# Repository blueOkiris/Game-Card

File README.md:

# Game Card

## Description

A business card sized portable game console utilizing buttons, multiple games, and an i2c display

[YouTube Video](https://www.youtube.com/watch?v=qE-Pg2zxOUw)

## Improving the Design (HELP!)

Right now I'm trying to redesign a new version where I can source all the electronics from manufacturers for a few reasons including:
 * Putting them up for sale
 * Decreasing cost
 * Simplifying build time

I've got everything redesigned and sourced except for the display. These little OLEDs are available everywhere except distributers it seems, and while they're like \$1-3 usually, I can't find sourcable ones for PCBs under \$10.

When the rest of the electronics costs \$4 total, it seems insane for it to be almost $15 to make.

If you can find a source I can use to build this, PLEASE let me know!

## Game List

Currently there are three games developed for the Game Card:

- Ping (1 and 2 player pong clone)
- Snek (Snake clone)
- In Progress: Tiny RPG (a very small RPG)

## More Links
 - [Info on Design](/docs/DESIGN.md)
 - [Info on Programming Cartridges](/docs/PROGRAMMING.md)
 - [Hackaday Project Page](https://hackaday.io/project/178686-game-card)

NOTE: If you're looking for the PCB designs and parts for the cartridges and cards, they're on the hackaday page

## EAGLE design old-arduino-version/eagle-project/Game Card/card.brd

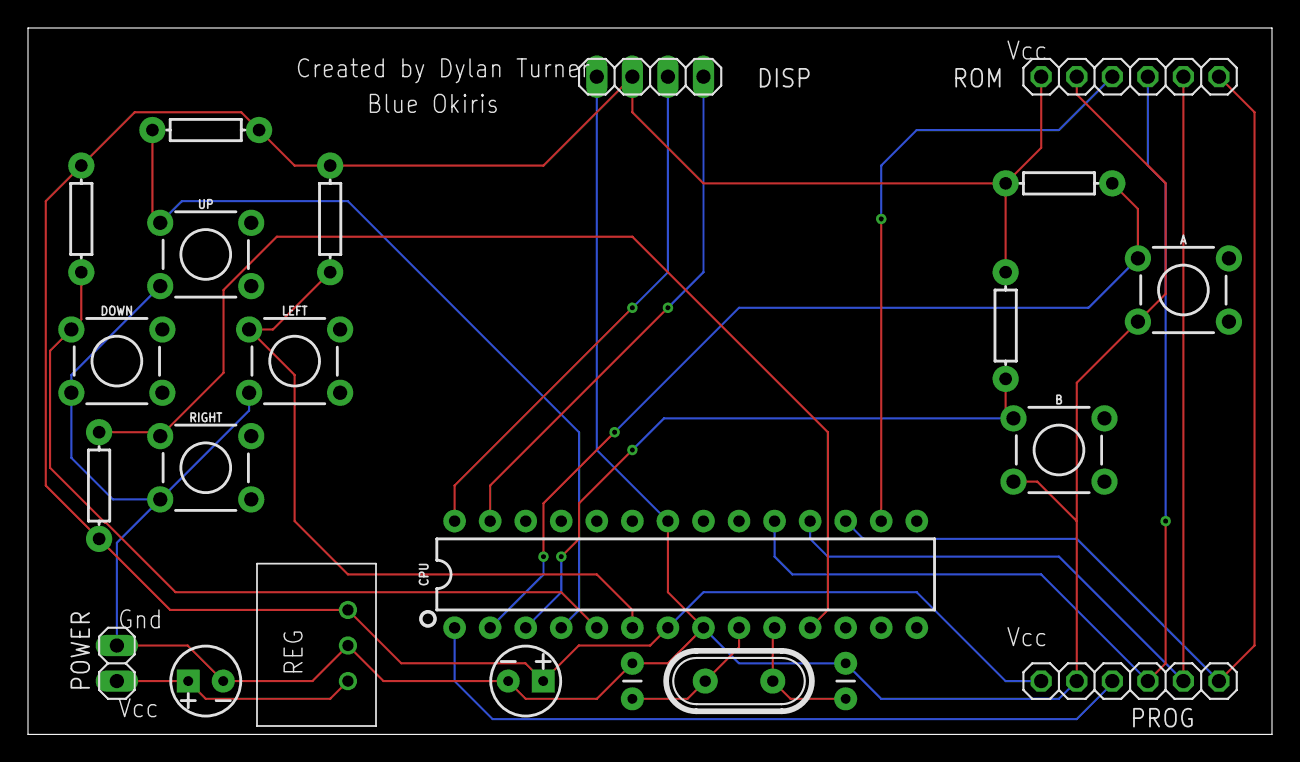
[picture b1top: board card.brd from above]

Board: 2 copper layers, 88.9 x 50.5 mm, 23 parts (0 on the bottom side), 18 nets.

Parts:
A: MOMENTARY-SWITCH-SPST-PTH-6.0MM; TACTILE_SWITCH_PTH_6.0MM
B: MOMENTARY-SWITCH-SPST-PTH-6.0MM; TACTILE_SWITCH_PTH_6.0MM
C1, C2: 10uF; CPOL-RADIAL-2.5MM-5MM
C3, C4: 22pF; CAP-PTH-2.54
CPU: 328P; DIP28
DISP: 1X04
DOWN: MOMENTARY-SWITCH-SPST-PTH-6.0MM; TACTILE_SWITCH_PTH_6.0MM
LEFT: MOMENTARY-SWITCH-SPST-PTH-6.0MM; TACTILE_SWITCH_PTH_6.0MM
POWER: 1X02
PROG: 1X06
R1, R2, R3, R4, R5, R6: 1k; AXIAL-0.3
REG: R-78E5.0-1.0; DC-DC_CONVERTER_78XX
RIGHT: MOMENTARY-SWITCH-SPST-PTH-6.0MM; TACTILE_SWITCH_PTH_6.0MM
ROM: 1X06
UP: MOMENTARY-SWITCH-SPST-PTH-6.0MM; TACTILE_SWITCH_PTH_6.0MM
X1: CRYSTALS-NOGND-HC49; HC49

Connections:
GND: A.3, B.3, C1.2, C2.2, C3.2, C4.2, CPU.8, CPU.22, DISP.1, DOWN.3, LEFT.3, POWER.1, PROG.2, REG.GND, RIGHT.3, ROM.2, UP.3
unnamed: CPU.17, PROG.6, ROM.6
unnamed: CPU.18, PROG.5, ROM.5
unnamed: CPU.19, PROG.4, ROM.4
unnamed: CPU.1, PROG.3
unnamed: A.1, CPU.2, R6.P$1
unnamed: C2.1, POWER.2, REG.VIN
unnamed: CPU.16, ROM.3
unnamed: CPU.28, DISP.3
unnamed: CPU.27, DISP.4
unnamed: C4.1, CPU.9, X1.2
unnamed: B.1, CPU.3, R5.P$1
unnamed: CPU.4, R4.P$1, UP.1
unnamed: CPU.5, DOWN.1, R3.P$1
unnamed: CPU.6, LEFT.1, R2.P$1
unnamed: CPU.11, R1.P$1, RIGHT.1
unnamed: C3.1, CPU.10, X1.1
VCC: C1.1, CPU.7, DISP.2, PROG.1, R1.P$2, R2.P$2, R3.P$2, R4.P$2, R5.P$2, R6.P$2, REG.VOUT, ROM.1

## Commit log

2020-12-14 Added so-far of project with video programming 'complete'
2020-12-14 Added defs for memory lengths
2020-12-15 Added gitignore to well, ignore stuff
2020-12-15 Started over now that I know the display draws columns, not rows
2020-12-15 Removed yield statements
2020-12-16 Fixed display driver code
2020-12-16 Added tile fill test
2020-12-16 Integrated SSD1306 driver into OLED wrapper
2020-12-16 Got basic setup working
2020-12-16 Created basic line demo
2020-12-16 Provided interface for setting display memory
2020-12-16 Fixed sprite and tile based graphics
2020-12-16 Started working on instruction interface
2020-12-16 Improved graphics interface and added more commands
2020-12-16 Major restructuring of project so it will be easier to implement loop structures
2020-12-17 Added registers and control flow instructions
2020-12-17 Bug fixes and working loops in demo
2020-12-17 Added documentation on programming ROMs
2020-12-17 Added info on creating ROMs
2020-12-17 Added info on register sizes and added note about additional instructions to add
2020-12-17 Implemented relative setting with -, *, /, <<, and >>
2020-12-17 Implemented reading instructions off of an eeprom
2020-12-17 Added planned instructions
2020-12-17 Added gitignore stuff for rom writer code
2020-12-17 Added setup for rom-writer tool
2020-12-17 Implemented a basic serial reader
2020-12-17 Achieved communication with Arduino over serial in c#
2020-12-17 Finished host-pc-side of rom transfer
2020-12-17 Added rom writing part of rom-writer
2020-12-17 Added C# project for writing assembler
2020-12-17 Added ebnf for assembler
2020-12-17 Added files intended for use in assembler application
2020-12-17 Finished lexer
2020-12-17 Finished parser for assembler
2020-12-17 Set up loop for code generation and successfully retrieved label indices
2020-12-18 Successfully implemented tile command
2020-12-18 Implemented background tile setting
2020-12-18 Implemented mov, add, sub, etc instructions to assembly language
2020-12-18 Implemented spr instruction in assembler
2020-12-18 Implemented spri instruction in assembler
2020-12-18 Implemented upd instruction in assembler
2020-12-18 Implemented compare command
2020-12-18 Implemented jump command in assembly
2020-12-18 Had to switch to 25LC512 instead of 1024 which means a 16-bit address instead of a 24-bit address, so I've adjusted code to work with that
2020-12-18 Added assembly guide
2020-12-18 Added board files to project
2020-12-20 Implemented buttons. Buttons are read from PORTD and placed in register 0. This can of course be changed, but that's how the PCB is set up
2020-12-21 Modified example program to use buttons
2020-12-21 Updated testApp code (and fixed bug problem)
2020-12-21 Some bug fixes
2020-12-21 Fixed game
2020-12-21 Remade ino to use eeprom
2020-12-27 Added test program for debugging memory chip
2020-12-28 Successfully implemented a system for writing to and reading from rom and made tester program
2020-12-28 Successfully transferred program to rom chip and checked that it was on there!
2020-12-28 Sped up rom reading
2020-12-28 More speed improvements
2020-12-28 Removed unnecessary read function from rom
2020-12-28 Bug fixes
2021-03-24 Shifted towards development for the pico
2021-03-24 Implemented oled api
2021-03-24 Implemented input system
2021-03-24 Implemented multicore example test
2021-03-24 Reorganized code in main file
2021-03-24 Added placeholder file for virtual machine
2021-03-24 Made the old arduino code into a zip instead of folder
2021-03-25 Implemented 'rom' system with 23A1024 SRAM chip. These will be on the 'cartridges '
2021-03-25 Created interfaces for the hardware so that VirtualMachine will be able to have different implementations. For instance instead of Oled, Buttons, and 23A1024, somebody could use an LCD, an analog sti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
2021-03-25 Started work on multicore virtual machine
2021-03-25 Implemented display control on second thread
2021-03-25 Added reading in program from cartridge
2021-03-25 Moved rom to a common folder so I can use it for making the writer
2021-03-25 Moved main source into game-card subfolder
2021-03-25 Added rom-writer project
2021-03-25 Added dependency on pico-sdk
2021-03-25 Added pc part of rom-writer system
2021-03-25 Implemented rom-writer pc component
2021-03-25 ROM writer not working, but implemented
2021-03-26 Changed rom writer to be an Arduino program sense Pico usb serial doesn't seem to work with C# library
2021-03-26 Removed old writer project from makefile
2021-03-26 Removed common dir since rom writer is not making use of it
2021-03-26 Attemptes to fix rom writer still not working
2021-03-26 Switched to game specific game writing programs; succesfull program running
2021-03-26 Fixed example so tiles go all the way to screen
2021-03-26 Added clear and return on application end for game
2021-03-26 Implemented controller input in interpreter
2021-03-26 Added size to rom chip so when changing chips, I can programatically get the value instead of having to change a lot of things
2021-03-26 Implemented 512kb EEPROM implementation of rom chip to be used with 25LC512; switched to new chip
2021-03-28 Started on assembler: made project, defined ebnf, and updated example.gca to match new assembly
2021-03-28 Removed accidentally added binary
2021-03-28 Set up main process of project and created main 3 classes
2021-03-28 Set up basic flow of lexer and top level parser
2021-03-28 Implemented string lexing
2021-03-29 Implemented identifer/keyword/command parser
2021-03-29 Implemented integer lexing
2021-03-29 Completed lexing step of parser
2021-03-29 Implemented include, added optional -p <folder> project folder argument
2021-03-29 Implemented instructions, arg lists, and args
2021-03-29 Fixed bugs
2021-03-29 Completed parser
2021-03-29 Implemented labels system
2021-03-29 Implemented jump and label replacement after code generation
2021-03-29 Added switch for all commands. On to the actual interpretation
2021-03-29 Added slightly better build instructions
2021-03-29 Fixed format error in readme
2021-03-29 Successfully implemented code generation for tile instruction
2021-03-29 Implemented (untested) update instruction
2021-03-29 Implemented (untested) compare instruction
2021-03-29 Changed delay to have a register option
2021-03-29 Implemented (untested) delay instruction
2021-03-29 Implemented (untested) jumps
2021-03-29 Added missing catch
2021-03-29 Noted all options for arguments for the value changing instructions
2021-03-29 Implemented mov for spr
2021-03-29 Implemented (untested) mov for spi, bg, spx, and spy
2021-03-29 Finished mov instruction
2021-03-29 Implemented (untested) the rest of the set insts, meaning implemented the rest of the insts
2021-03-29 Bug fixes. Example compiles. Untested though
2021-03-29 Added pictures to read me and moved version one info to bottom
2021-03-30 Added image of v2 PCB
2021-03-30 Added image of cartridge PCB
2021-03-30 Added eagle project to repo
2021-04-02 Renamed current rom chip to correct name
2021-04-06 Fixed eeprom writing
2021-04-06 Redid rom read/write stuff
2021-07-23 Nuked pico version and switched to cartridge-with-arduino version. Also moved disp code into header (still set up for PICO I2C lib though)
2021-07-23 Updated description for arduino
2021-07-23 Added info on setting up programming environment
2021-07-23 Converted Display library to work with ATtiny84 and TinyWireM and created program to run the Oled test function (which compiles)
2021-07-23 Updated name of display lib since it will now go in people's library folder
2021-07-23 Updated author information for game card display files
2021-07-26 Switched to SoftwareWire library because I could actually get it working and it's built in.
2021-07-27 Adjusted libraries and code to get controller + display example working (which it does!)
2021-08-03 Added test program for cart board that will show it's been programmed correctly
2021-08-03 Fixed TestOled
2021-08-04 Added Pong game (and adjusted code as necessary).
2021-08-04 Adjusted Ping code
2021-08-04 Started working on Snake. Incomplete. Will be tough to fit into such a small space
2021-08-04 Finished implementing Snake clone
2021-08-04 Added more specific details on burning bootloader to readme
2021-08-04 Moved test programs into their own folder to make root folder more clear
2021-08-04 Updated readme to remove reference to A and B
2021-08-04 Fixed distinction in code
2021-08-04 Temp rename
2021-08-04 Fixed double folder glitch
2021-08-04 Improved documentation
2021-08-11 Updated readme to add final picture of the game card
2021-08-17 Started on tiny rpg that can fit into the 8kB
2021-08-17 Switched to TinyWireM since it's significantly smaller than SoftwareWire
2021-08-17 Fixed Ping after switching to new faster library
2021-08-17 Removed unstarted TinyRPG project
2021-08-17 Removed sends with writes instead
2021-08-17 Modified repo to utilize self-contained cli tools to upload to game card (and to manage libraries) instead of having to manually copy paste libraries and open up Arduino IDE. It also allows for easie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
2021-08-17 Added note for linux users about changing data and downloads paths to match POSIC
2021-08-17 Added target which allows me to run the test inos since arduino-cli had made them unrunnable
2021-08-19 Added research into building my own driver into the game card
2021-08-19 Added adafruit reference image
2021-08-19 Added another i2c circuit
2021-08-19 Added plea for help

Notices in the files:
parts and their libraries:
SparkFun-Switches: Licensing: Creative Commons ShareAlike 4.0 International - https://creativecommons.org/licenses/by-sa/4.0
